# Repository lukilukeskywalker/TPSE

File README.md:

# TPSE
In my university they love to reinvent the wheel... Heck, they love letting their students
reinvent the wheel... So much, that probably, it is the university that has created
the greatest ammount of diferent types of Arduino's. So here comes my version of it  
Presenting: 
# **_"The Most Useless Arduino"_**

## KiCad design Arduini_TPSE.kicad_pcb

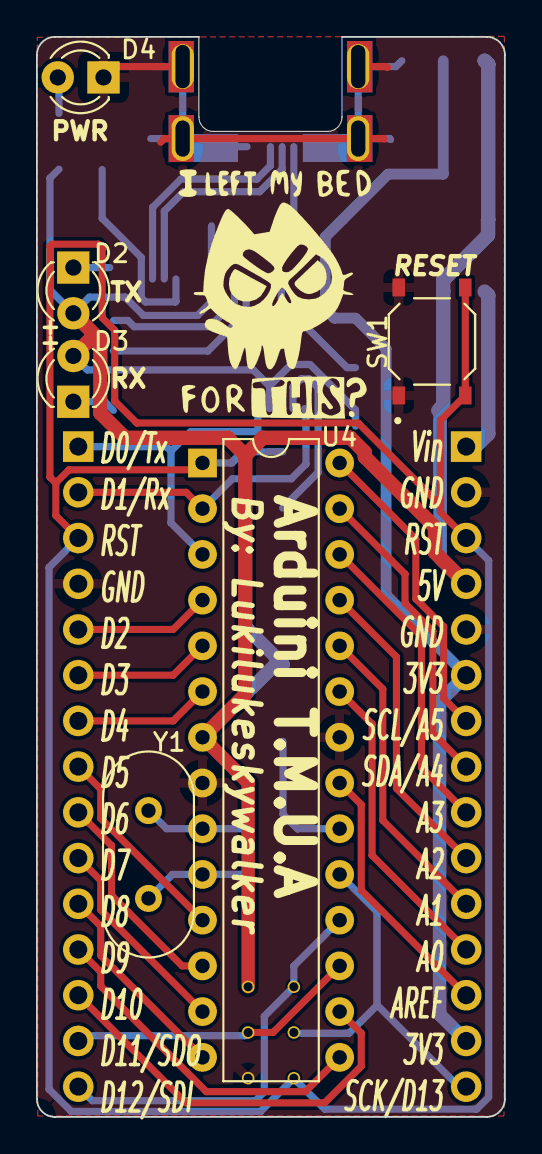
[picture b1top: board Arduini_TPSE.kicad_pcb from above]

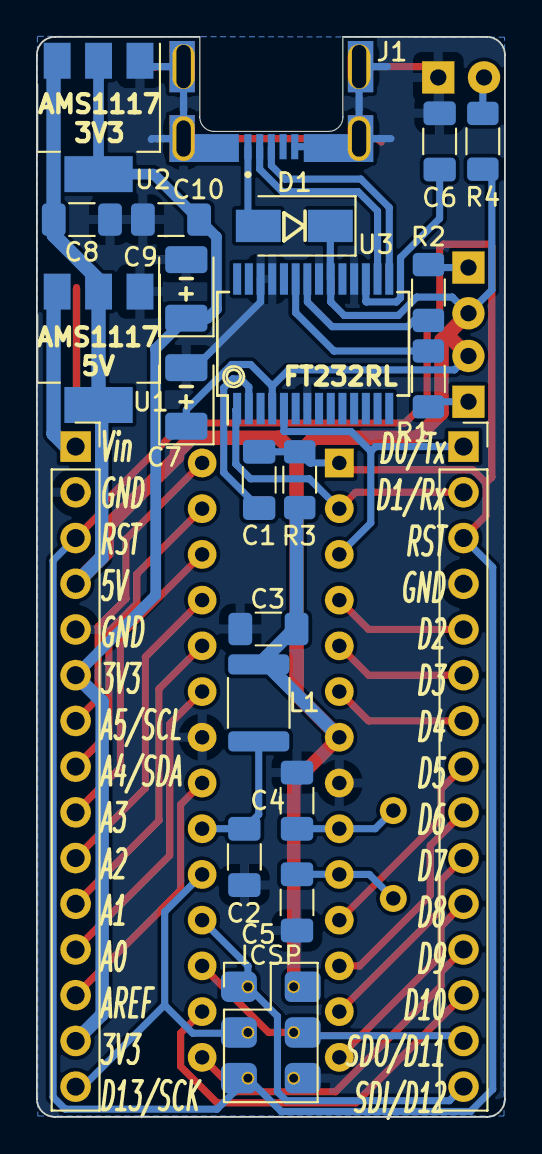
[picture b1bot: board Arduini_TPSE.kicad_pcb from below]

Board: 2 copper layers, 26.0 x 60.0 mm, 29 parts (23 on the bottom side), 39 nets.

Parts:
C1, C2, C3, C6, C8, C10: 100n; C_1206_3216Metric_Pad1.33x1.80mm_HandSolder
C4, C5: 22p; C_1206_3216Metric_Pad1.33x1.80mm_HandSolder
C7, C9: 100u; CP_EIA-3528-15_AVX-H_Pad1.50x2.35mm_HandSolder
D1: D_Schottky; D_SMA
D2: TX Green; LED_D3.0mm
D3: RX Red; LED_D3.0mm
D4: POWER_LED; LED_D3.0mm
J1: 2134441-2; TE_2134441-2
J2: ICSP; ICSP_Spring_Conn
L1: 100uH; L_1812_4532Metric
P1: Digital; PinSocket_1x15_P2.54mm_Vertical
P2: Analog; PinSocket_1x15_P2.54mm_Vertical
R1, R2, R4: 1K; R_1206_3216Metric_Pad1.30x1.75mm_HandSolder
R3: 10K; R_1206_3216Metric_Pad1.30x1.75mm_HandSolder
SW1: SW_Push; SW_PTS526_SM08_SMTR2_LFS
U1: AMS1117-5.0; SOT-223-3_TabPin2
U2: AMS1117-3.3; SOT-223-3_TabPin2
U3: FT232RL; SSOP-28_5.3x10.2mm_P0.65mm
U4: ATmega328-P; DIP-28_W7.62mm
Y1: 16Mhz; Crystal_HC49-4H_Vertical

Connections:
+3V3: C9.1, C10.1, P2.6, P2.14, U2.2 (VO)
+5V: C3.1, C7.1, C8.1, D1.1 (K), D2.2 (A), D3.2 (A), J2.2, L1.2, P2.4, R3.1, R4.1, U1.2 (VO), U2.3 (VI), U3.4 (VCCIO), U3.20 (VCC), U4.7 (VCC)
+5VA: C2.1, L1.1, U4.20 (AVCC)
/0(Rx): P1.2, U3.1 (TXD), U4.2 (PD0)
/1(Tx): P1.1, U3.5 (RXD), U4.3 (PD1)
/2: P1.5, U4.4 (PD2)
/3(**): P1.6, U4.5 (PD3)
/3V3OUT: C6.2, U3.17 (3V3OUT)
/4: P1.7, U4.6 (PD4)
/5(**): P1.8, U4.11 (PD5)
/6(**): P1.9, U4.12 (PD6)
/7: P1.10, U4.13 (PD7)
/8: P1.11, U4.14 (PB0)
/9(**): P1.12, U4.15 (PB1)
/10(**/SS): P1.13, U4.16 (PB2)
/11(**/MOSI): J2.4, P1.14, U4.17 (PB3)
/12(MISO): J2.1, P1.15, U4.18 (PB4)
/13(SCK): J2.3, P2.15, U4.19 (PB5)
/A0: P2.12, U4.23 (PC0)
/A1: P2.11, U4.24 (PC1)
/A2: P2.10, U4.25 (PC2)
/A3: P2.9, U4.26 (PC3)
/A4: P2.8, U4.27 (PC4)
/A5: P2.7, U4.28 (PC5)
/AREF: P2.13, U4.21 (AREF)
/D+: J1.3 (D+), U3.15 (USBD+)
/D-: J1.2 (D-), U3.16 (USBD-)
/Reset: C1.2, J2.5, P1.3, P2.3, R3.2, SW1.2, U4.1 (~RESET/PC6)
/Vin: P2.1, U1.3 (VI)
GND: C2.2, C3.2, C4.2, C5.2, C6.1, C7.2, C8.2, C9.2, C10.2, D4.1 (K), J1.5 (GND), J1.S1 (SHIELD), J1.S2 (SHIELD), J1.S3 (SHIELD), J1.S4 (SHIELD), J2.6, P1.4, P2.2, P2.5, SW1.1, U1.1 (GND), U2.1 (GND), U3.7 (GND), U3.18 (GND), U3.21 (GND), U3.25 (AGND), U3.26 (TEST), U4.8 (GND), U4.22 (GND)
unnamed: C1.1, U3.2 (DTR)
unnamed: C4.1, U4.9 (XTAL1/PB6), Y1.2
unnamed: C5.1, U4.10 (XTAL2/PB7), Y1.1
unnamed: D1.2 (A), J1.1 (VBUS)
unnamed: D2.1 (K), R2.2
unnamed: D3.1 (K), R1.2
unnamed: D4.2 (A), R4.2
unnamed: R1.1, U3.23 (CBUS0)
unnamed: R2.1, U3.22 (CBUS1)

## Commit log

2022-03-12 Proyecto finalizado en Kicad
2022-03-14 Condensadores 3V3, 5V, y recolocacion
2022-03-29 Ampliacion
2022-03-29 Final
2022-05-02 Version presentada
